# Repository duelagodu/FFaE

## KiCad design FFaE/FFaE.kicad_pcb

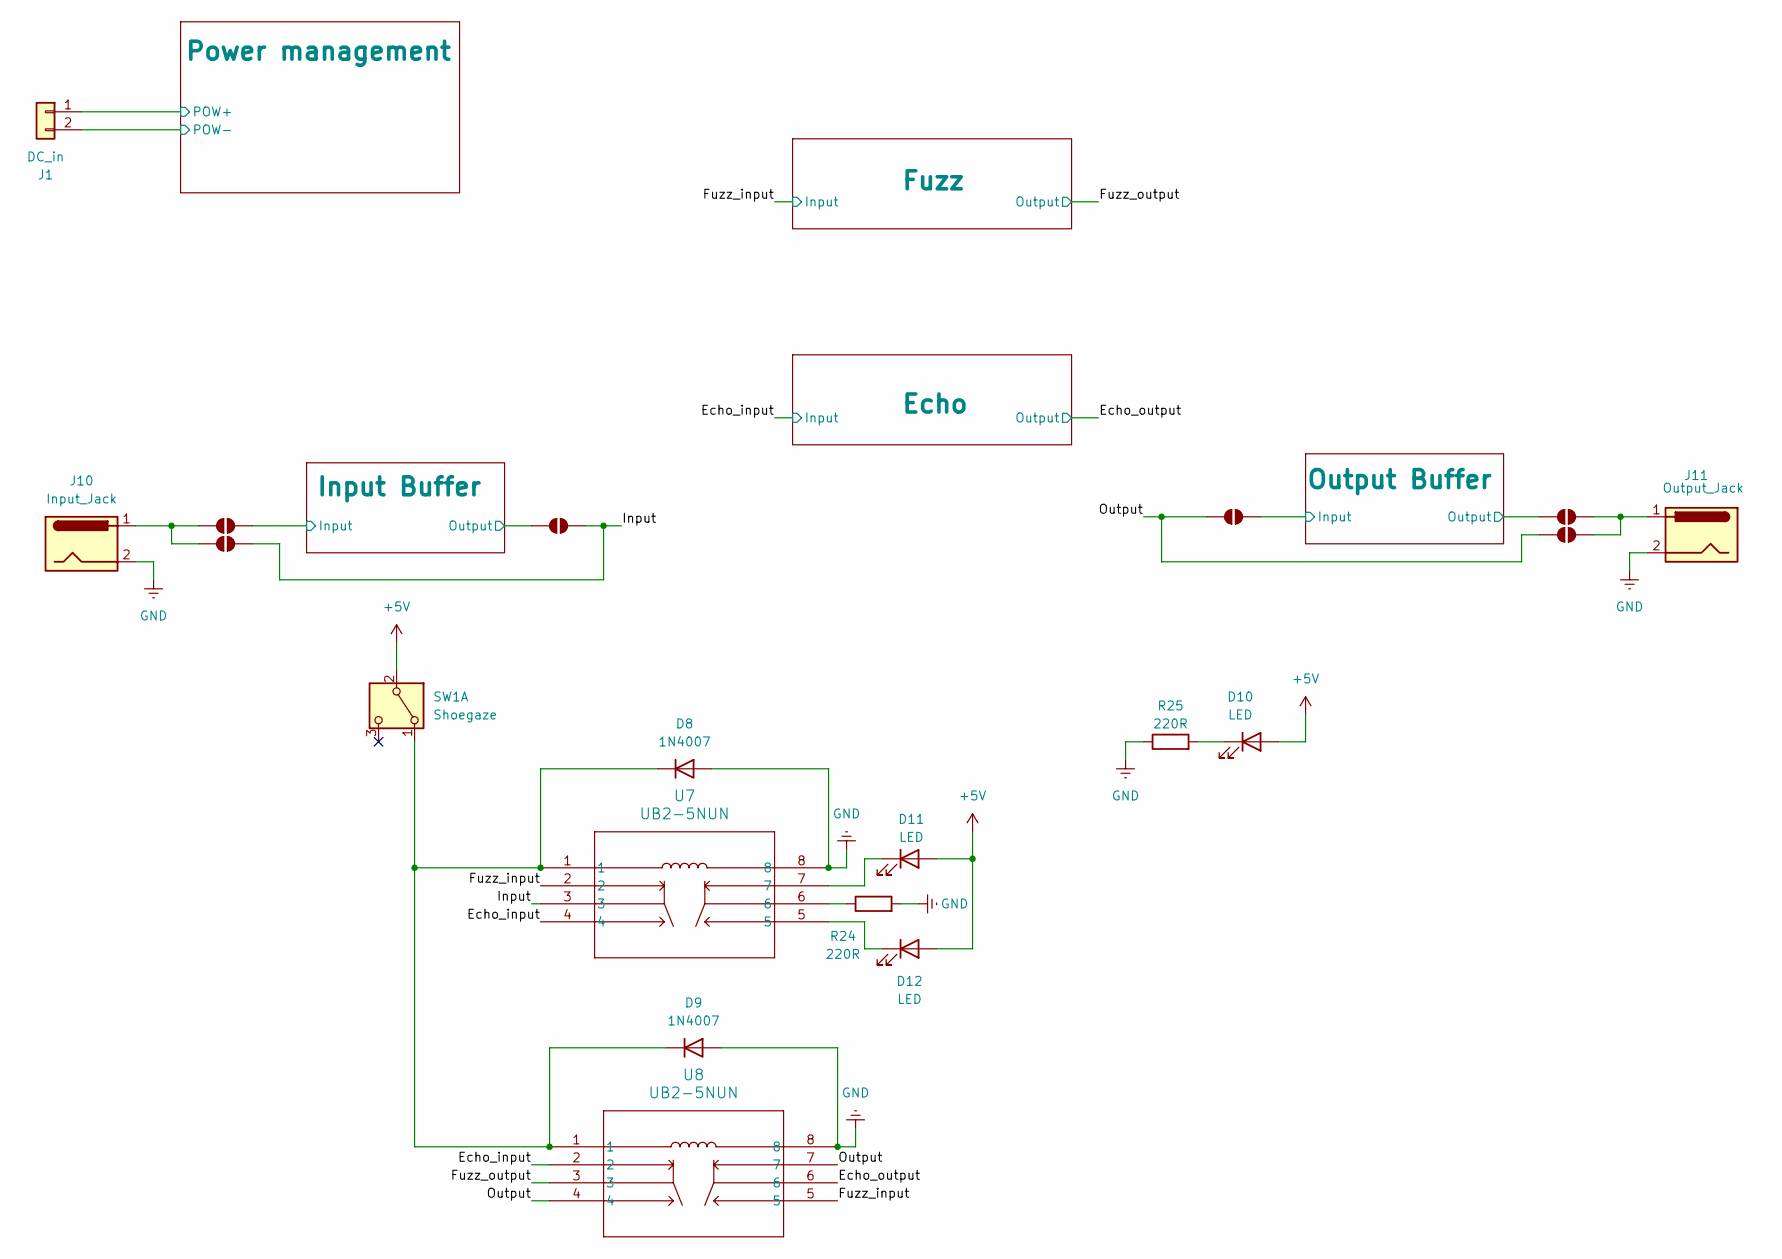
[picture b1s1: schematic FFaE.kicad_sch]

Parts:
D8, D9: 1N4007; D_DO-41_SOD81_P10.16mm_Horizontal
D10, D11, D12: LED; JST_PH_B2B-PH-K_1x02_P2.00mm_Vertical
J1: DC_in; JST_PH_B2B-PH-K_1x02_P2.00mm_Vertical
J10: Input_Jack; JST_PH_B2B-PH-K_1x02_P2.00mm_Vertical
J11: Output_Jack; JST_PH_B2B-PH-K_1x02_P2.00mm_Vertical
JP1, JP2, JP3, JP4, JP5, JP6: SolderJumper_2_Open; SolderJumper-2_P1.3mm_Open_RoundedPad1.0x1.5mm
R24, R25: 220R; R_Axial_DIN0207_L6.3mm_D2.5mm_P7.62mm_Horizontal
SW1: Shoegaze; JST_PH_B2B-PH-K_1x02_P2.00mm_Vertical
U7, U8: UB2-5NUN

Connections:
+5V: D10.2 (A), D11.2 (A), D12.2 (A), SW1.2 (B); also elsewhere on the board
/Echo_input: U7.4, U8.2; also elsewhere on the board
/Echo_output: U8.6; also elsewhere on the board
/Fuzz_input: U7.2, U8.5; also elsewhere on the board
/Fuzz_output: U8.3; also elsewhere on the board
/Input: JP2.2 (B), JP5.2 (B), U7.3
/Input Buffer/Input: JP1.2 (B); also elsewhere on the board
/Input Buffer/Output: JP5.1 (A); also elsewhere on the board
/Output: JP4.1 (A), JP6.1 (A), U8.4, U8.7
/Output Buffer/Input: JP6.2 (B); also elsewhere on the board
/Output Buffer/Output: JP3.1 (A); also elsewhere on the board
/Power management/POW+: J1.1; also elsewhere on the board
/Power management/POW-: J1.2; also elsewhere on the board
GND: D8.2 (A), D9.2 (A), J10.2, J11.2, R24.2, R25.1, U7.8, U8.8; also elsewhere on the board
unnamed: D8.1 (K), D9.1 (K), SW1.1 (A), U7.1, U8.1
unnamed: D10.1 (K), R25.2
unnamed: D11.1 (K), U7.7
unnamed: D12.1 (K), U7.5
unnamed: J10.1, JP1.1 (A), JP2.1 (A)
unnamed: J11.1, JP3.2 (B), JP4.2 (B)
unnamed: R24.1, U7.6

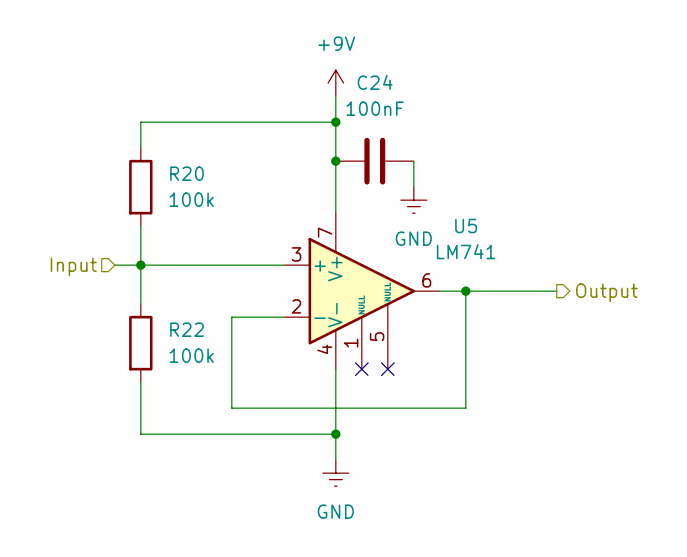
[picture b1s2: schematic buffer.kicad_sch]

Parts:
C24: 100nF; C_Rect_L4.0mm_W2.5mm_P2.50mm
R20, R22: 100k; R_Axial_DIN0207_L6.3mm_D2.5mm_P7.62mm_Horizontal
U5: LM741; DIP-8_W7.62mm

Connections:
+9V: C24.2, R20.1, U5.7 (V+); also elsewhere on the board
/Input Buffer/Input: R20.2, R22.1, U5.3 (+); also elsewhere on the board
/Input Buffer/Output: U5.2 (-), U5.6; also elsewhere on the board
GND: C24.1, R22.2, U5.4 (V-); also elsewhere on the board

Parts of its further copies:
C25: 100nF; C_Rect_L4.0mm_W2.5mm_P2.50mm
R21, R23: 100k; R_Axial_DIN0207_L6.3mm_D2.5mm_P7.62mm_Horizontal
U6: LM741; DIP-8_W7.62mm

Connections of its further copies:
+9V: C25.2, R21.1, U6.7 (V+); also elsewhere on the board
/Output Buffer/Input: R21.2, R23.1, U6.3 (+); also elsewhere on the board
/Output Buffer/Output: U6.2 (-), U6.6; also elsewhere on the board
GND: C25.1, R23.2, U6.4 (V-); also elsewhere on the board

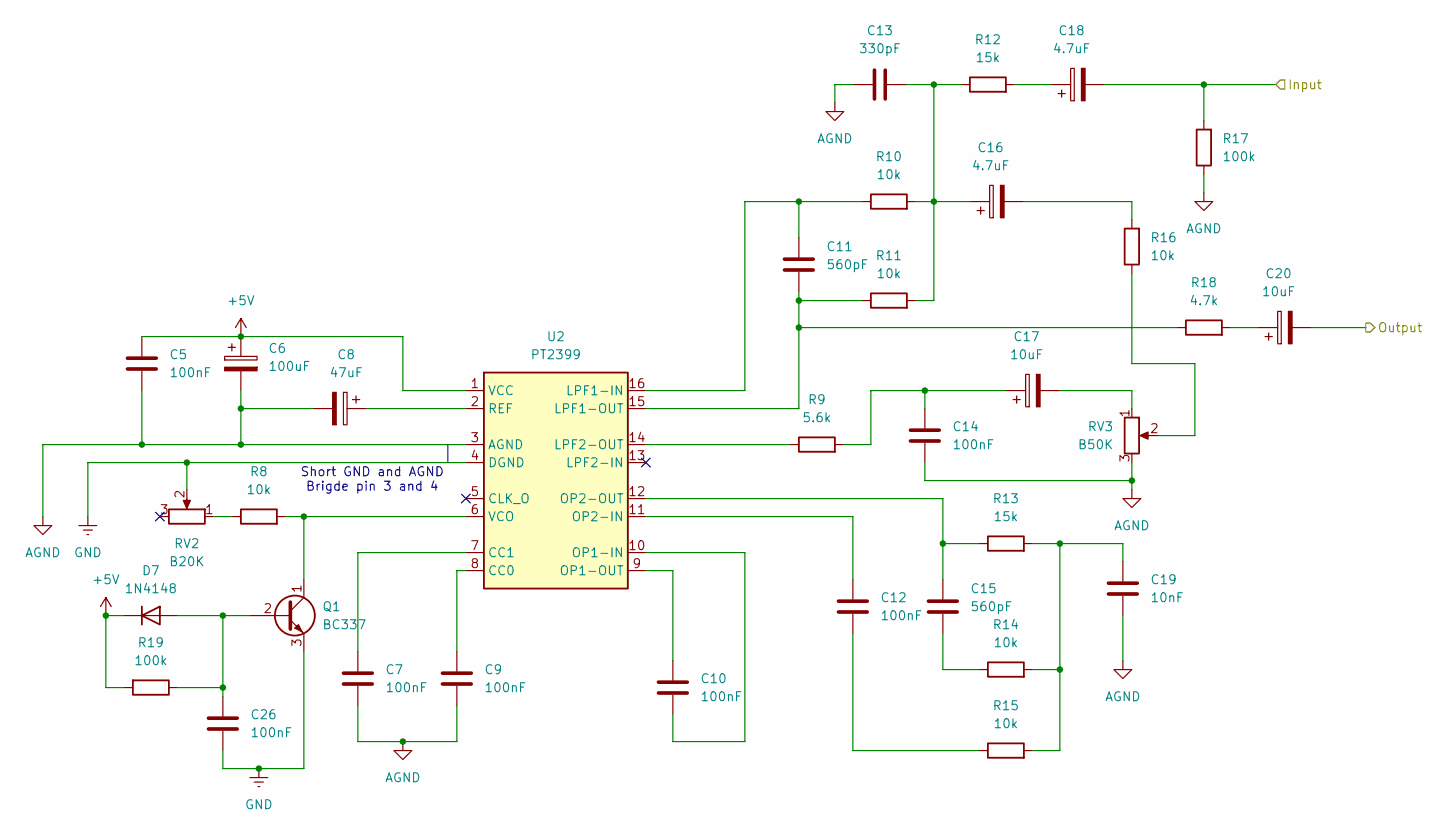
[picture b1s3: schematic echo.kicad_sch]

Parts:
C5, C7, C9, C10, C12, C14, C26: 100nF; C_Rect_L4.0mm_W2.5mm_P2.50mm
C6: 100uF; CP_Radial_D8.0mm_P5.00mm
C8: 47uF; CP_Radial_D5.0mm_P2.50mm
C11, C15: 560pF; C_Rect_L4.0mm_W2.5mm_P2.50mm
C13: 330pF; C_Rect_L4.0mm_W2.5mm_P2.50mm
C16, C18: 4.7uF; CP_Radial_D5.0mm_P2.00mm
C17, C20: 10uF; CP_Radial_D5.0mm_P2.00mm
C19: 10nF; C_Rect_L4.0mm_W2.5mm_P2.50mm
D7: 1N4148; D_DO-35_SOD27_P7.62mm_Horizontal
Q1: BC337; TO-92_Inline
R8, R10, R11, R14, R15, R16: 10k; R_Axial_DIN0207_L6.3mm_D2.5mm_P7.62mm_Horizontal
R9: 5.6k; R_Axial_DIN0207_L6.3mm_D2.5mm_P7.62mm_Horizontal
R12, R13: 15k; R_Axial_DIN0207_L6.3mm_D2.5mm_P7.62mm_Horizontal
R17, R19: 100k; R_Axial_DIN0207_L6.3mm_D2.5mm_P7.62mm_Horizontal
R18: 4.7k; R_Axial_DIN0207_L6.3mm_D2.5mm_P7.62mm_Horizontal
RV2: B20K; JST_PH_B2B-PH-K_1x02_P2.00mm_Vertical
RV3: B50K; JST_PH_B3B-PH-K_1x03_P2.00mm_Vertical
U2: PT2399; DIP-16_W7.62mm

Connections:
+5V: C5.1, C6.1, D7.1 (K), R19.2, U2.1 (VCC); also elsewhere on the board
/Echo_input: C18.2, R17.2; also elsewhere on the board
/Echo_output: C20.2; also elsewhere on the board
AGND: C5.2, C6.2, C7.2, C8.2, C9.2, C13.1, C14.1, C19.2, R17.1, RV3.3, U2.3 (AGND)
GND: C26.2, Q1.3 (E), RV2.2, U2.4 (DGND); also elsewhere on the board
unnamed: C12.2, R15.1
unnamed: C13.2, C16.1, R10.2, R11.2, R12.1
unnamed: C14.2, C17.1, R9.2
unnamed: C15.1, R14.1
unnamed: C16.2, R16.2
unnamed: C17.2, RV3.1
unnamed: C18.1, R12.2
unnamed: C19.1, R13.2, R14.2, R15.2
unnamed: C20.1, R18.2
unnamed: C26.1, D7.2 (A), Q1.2 (B), R19.1
unnamed: Q1.1 (C), R8.2, U2.6 (VCO)
unnamed: R8.1, RV2.1
unnamed: R16.1, RV3.2
unnamed: C9.1, U2.8 (CC0)
unnamed: C7.1, U2.7 (CC1)
unnamed: C11.2, R10.1, U2.16 (LPF1-IN)
unnamed: C11.1, R11.1, R18.1, U2.15 (LPF1-OUT)
unnamed: R9.1, U2.14 (LPF2-OUT)
unnamed: C10.2, U2.10 (OP1-IN)
unnamed: C10.1, U2.9 (OP1-OUT)
unnamed: C12.1, U2.11 (OP2-IN)
unnamed: C15.2, R13.1, U2.12 (OP2-OUT)
unnamed: C8.1, U2.2 (REF)

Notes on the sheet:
Short GND and AGND Brigde pin 3 and 4

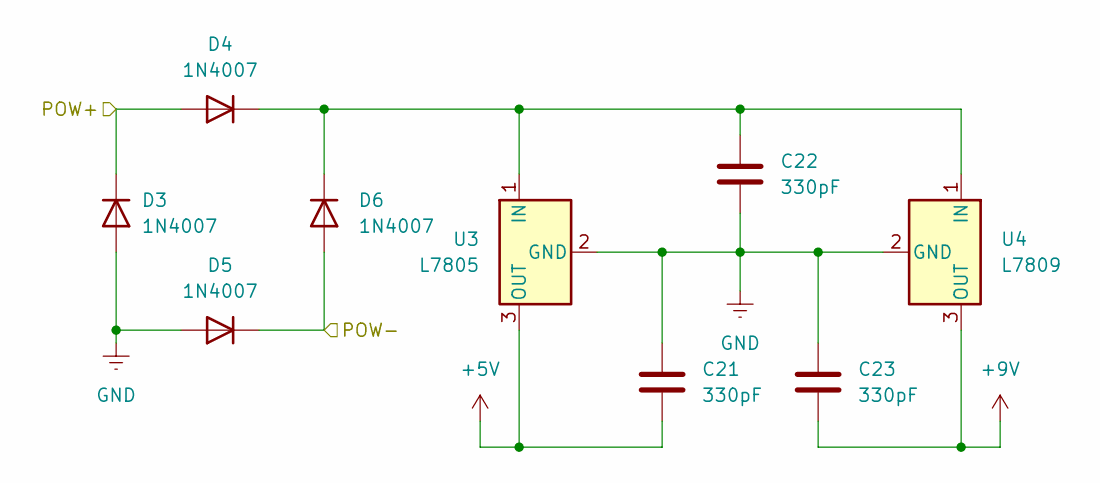
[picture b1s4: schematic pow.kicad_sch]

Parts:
C21, C22, C23: 330pF; C_Rect_L4.0mm_W2.5mm_P2.50mm
D3, D4, D5, D6: 1N4007; D_DO-41_SOD81_P10.16mm_Horizontal
U3: L7805; TO-220-3_Vertical
U4: L7809; TO-220-3_Vertical

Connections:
+5V: C21.1, U3.3 (OUT); also elsewhere on the board
+9V: C23.1, U4.3 (OUT); also elsewhere on the board
/Power management/POW+: D3.1 (K), D4.2 (A); also elsewhere on the board
/Power management/POW-: D5.1 (K), D6.2 (A); also elsewhere on the board
GND: C21.2, C22.1, C23.2, D3.2 (A), D5.2 (A), U3.2 (GND), U4.2 (GND); also elsewhere on the board
unnamed: C22.2, D4.1 (K), D6.1 (K), U3.1 (IN), U4.1 (IN)

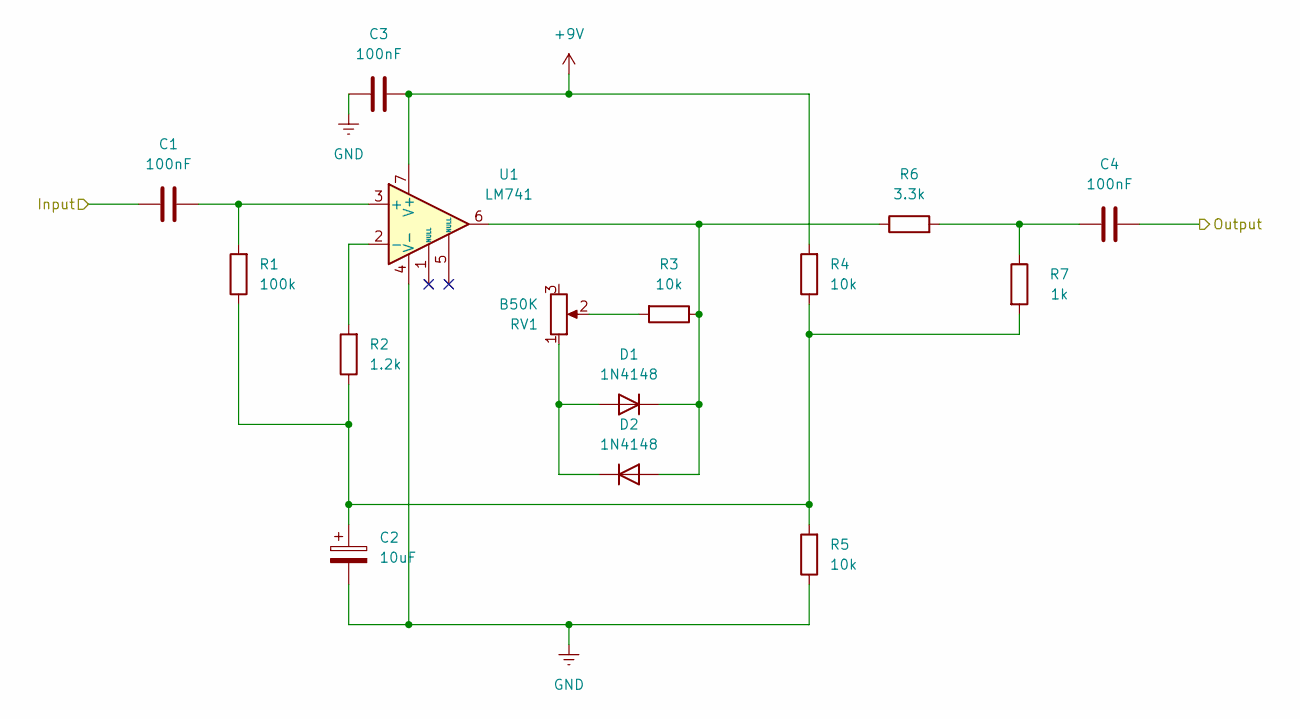
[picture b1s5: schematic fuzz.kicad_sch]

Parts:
C1, C3, C4: 100nF; C_Rect_L4.0mm_W2.5mm_P2.50mm
C2: 10uF; CP_Radial_D5.0mm_P2.00mm
D1, D2: 1N4148; D_DO-35_SOD27_P7.62mm_Horizontal
R1: 100k; R_Axial_DIN0207_L6.3mm_D2.5mm_P7.62mm_Horizontal
R2: 1.2k; R_Axial_DIN0207_L6.3mm_D2.5mm_P7.62mm_Horizontal
R3, R4, R5: 10k; R_Axial_DIN0207_L6.3mm_D2.5mm_P7.62mm_Horizontal
R6: 3.3k; R_Axial_DIN0207_L6.3mm_D2.5mm_P7.62mm_Horizontal
R7: 1k; R_Axial_DIN0207_L6.3mm_D2.5mm_P7.62mm_Horizontal
RV1: B50K; JST_PH_B2B-PH-K_1x02_P2.00mm_Vertical
U1: LM741; DIP-8_W7.62mm

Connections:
+9V: C3.2, R4.2, U1.7 (V+); also elsewhere on the board
/Fuzz_input: C1.1; also elsewhere on the board
/Fuzz_output: C4.1; also elsewhere on the board
GND: C2.2, C3.1, R5.1, U1.4 (V-); also elsewhere on the board
unnamed: C2.1, R1.1, R2.1, R4.1, R5.2, R7.2
unnamed: C4.2, R6.2, R7.1
unnamed: D1.2 (A), D2.1 (K), RV1.1
unnamed: D1.1 (K), D2.2 (A), R3.1, R6.1, U1.6
unnamed: R3.2, RV1.2
unnamed: C1.2, R1.2, U1.3 (+)
unnamed: R2.2, U1.2 (-)

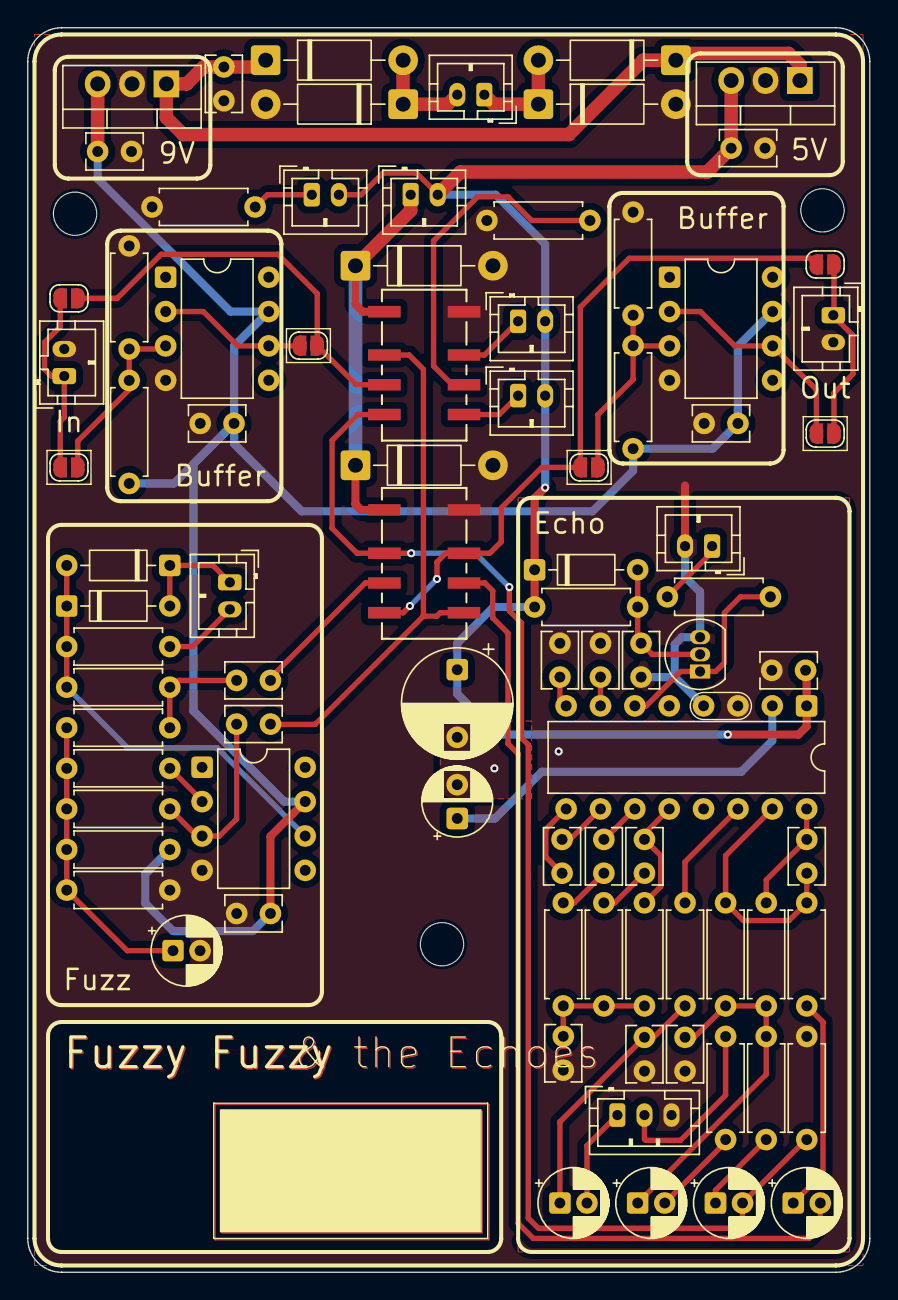
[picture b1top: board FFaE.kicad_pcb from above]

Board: 2 copper layers, 62.2 x 92.0 mm, 85 parts (0 on the bottom side), 54 nets.

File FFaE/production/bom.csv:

Designator,Footprint,Quantity,Value,LCSC Part #
"_2, ",,2,,
"C1, C10, C12, C14, C24, C25, C26, C3, C4, C5, C7, C9",C_Rect_L4.0mm_W2.5mm_P2.50mm,12,100nF,
"C11, C15",C_Rect_L4.0mm_W2.5mm_P2.50mm,2,560pF,
"C13, C21, C22, C23",C_Rect_L4.0mm_W2.5mm_P2.50mm,4,330pF,
"C16, C18",CP_Radial_D5.0mm_P2.00mm,2,4.7uF,
"C17, C2, C20",CP_Radial_D5.0mm_P2.00mm,3,10uF,
C19,C_Rect_L4.0mm_W2.5mm_P2.50mm,1,10nF,
C6,CP_Radial_D8.0mm_P5.00mm,1,100uF,
C8,CP_Radial_D5.0mm_P2.50mm,1,47uF,
"D1, D2, D7",D_DO-35_SOD27_P7.62mm_Horizontal,3,1N4148,
"D10, D11, D12",JST_PH_B2B-PH-K_1x02_P2.00mm_Vertical,3,LED,
"D3, D4, D5, D6, D8, D9",D_DO-41_SOD81_P10.16mm_Horizontal,6,1N4007,
J1,JST_PH_B2B-PH-K_1x02_P2.00mm_Vertical,1,DC_in,
J10,JST_PH_B2B-PH-K_1x02_P2.00mm_Vertical,1,Input_Jack,
J11,JST_PH_B2B-PH-K_1x02_P2.00mm_Vertical,1,Output_Jack,
Q1,TO-92_Inline,1,BC337,
"R1, R17, R19, R20, R21, R22, R23",R_Axial_DIN0207_L6.3mm_D2.5mm_P7.62mm_Horizontal,7,100k,
"R10, R11, R14, R15, R16, R3, R4, R5, R8",R_Axial_DIN0207_L6.3mm_D2.5mm_P7.62mm_Horizontal,9,10k,
"R12, R13",R_Axial_DIN0207_L6.3mm_D2.5mm_P7.62mm_Horizontal,2,15k,
R18,R_Axial_DIN0207_L6.3mm_D2.5mm_P7.62mm_Horizontal,1,4.7k,
R2,R_Axial_DIN0207_L6.3mm_D2.5mm_P7.62mm_Horizontal,1,1.2k,
"R24, R25",R_Axial_DIN0207_L6.3mm_D2.5mm_P7.62mm_Horizontal,2,220R,
R6,R_Axial_DIN0207_L6.3mm_D2.5mm_P7.62mm_Horizontal,1,3.3k,
R7,R_Axial_DIN0207_L6.3mm_D2.5mm_P7.62mm_Horizontal,1,1k,
R9,R_Axial_DIN0207_L6.3mm_D2.5mm_P7.62mm_Horizontal,1,5.6k,
RV1,JST_PH_B2B-PH-K_1x02_P2.00mm_Vertical,1,B50K,
RV2,JST_PH_B2B-PH-K_1x02_P2.00mm_Vertical,1,B20K,
RV3,JST_PH_B3B-PH-K_1x03_P2.00mm_Vertical,1,B50K,
SW1,JST_PH_B2B-PH-K_1x02_P2.00mm_Vertical,1,Shoegaze,
"U1, U5, U6",DIP-8_W7.62mm,3,LM741,
U2,DIP-16_W7.62mm,1,PT2399,
U3,TO-220-3_Vertical,1,L7805,
U4,TO-220-3_Vertical,1,L7809,
"U7, U8",UB2-5NUN,2,UB2-5NUN,

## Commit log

2024-10-23 Adds rev 1.0 of schematic
2025-10-03 Dump
2025-10-21 PCB v0
